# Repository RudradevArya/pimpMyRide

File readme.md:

# Pimp My Ride - Part 3

## Arduino Speedometer and NeoPixel FastLED Strip

This project combines a speedometer functionality with an LED light controller for a bicycle or similar vehicle. It uses an Arduino board to read speed data from a magnetic sensor and control a series of LED light patterns.

## Project Progress Videos

## Task List

Here's a task list for further development of the project:

* [x] iNtErgRaTiOn (just for making fun of myself bcz in a hurry i couldn't type "integration" properly)
* [x] Implement basic speedometer functionality
* [x] Set up LCD display for speed and distance
* [x] Integrate WS2812B LED strip control
* [x] Create multiple LED patterns
* [x] Implement brake light feature
* [ ] Optimize code for better performance
* [ ] Implement power-saving features
* [x] Create a PCB design for a more compact build
* [ ] Develop a weatherproof enclosure
* [ ] Add Bluetooth connectivity for mobile app control
* [ ] Implement data logging feature
* [ ] Create user manual and assembly instructions
* [x] ✨**ENJOY**✨

## Features

1. Speedometer
    * Calculates and displays current speed
    * Tracks total distance traveled
    * Shows total time in motion
2. LED Light Controller
    * Multiple light patterns for visibility and aesthetics
    * Turn signal and brake light functionality
    * Customizable LED colors and patterns

## Hardware Requirements

* Arduino board (e.g., Arduino Uno)
* LCD display (16x2 characters)
* Magnetic sensor (Hall effect sensor)
* WS2812B LED strip
* Buttons for mode selection and turn signals
* Appropriate resistors and wiring

For a complete list of parts, refer to `tinkerCADParts list.png` in the project root.

## Wiring Diagram and Schematic

* The circuit diagram can be found in `tinkerCAD circuit diagram.png`
* The schematic is available in `tinker_cad-schematics.png`
* For the PCB design, refer to `KiCAD PCB screenshot.png`

For the most up-to-date schematic and PCB design, open the following files in KiCad:

* Schematic: `intergration/integration-arduino-shield/integration.kicad_sch`
* PCB: `intergration/integration-arduino-shield/integration.kicad_pcb`

## Libraries Used

* FastLED
* LiquidCrystal

## Pin Configuration

* LCD: pins 13, 12, 11, 10, 9, 8
* Magnetic sensor: pin 7
* LED strip data: pin 3
* Right turn signal button: pin 4
* Left turn signal button: pin 5
* Brake signal: pin 2
* Mode selection button: pin 13
* Main control button: pin 12

## Setup

1. Connect all components according to the pin configuration.
2. Install the required libraries in your Arduino IDE.
3. Upload the provided code to your Arduino board.
4. Adjust the `Wheel_circumference_in_Cm` constant to match your wheel size.

## Usage

* The speedometer will automatically start tracking when motion is detected.
* Use the mode selection button to cycle through different LED patterns.
* Use the turn signal buttons to activate left or right turn signals.
* The brake light will activate automatically when the brake signal is received.

## Customization

You can customize the LED patterns by modifying the `Pattern1()` through `Pattern9()` functions in the code. Adjust colors, timing, and sequences to create your desired effects.

## Project Structure

``` bash
PimpMyRide/
│
├── intergration/
│   ├── integration-arduino-shield/ (run the .pcb & .sch files from here)
│       ├── integration.kicad_sch
│       ├── integration.kicad_pcb
│
├── intergration.ino (the main arduino file to run)
├── tinkerCAD circuit diagram.png
├── tinkerCADParts list.png
├── tinker_cad-schematics.png
├── KiCAD PCB screenshot.png
└── README.md
```

## Note

This project combines multiple functionalities and may require fine-tuning based on your specific hardware setup and requirements. Always ensure proper visibility and adhere to local regulations when using this on public roads.

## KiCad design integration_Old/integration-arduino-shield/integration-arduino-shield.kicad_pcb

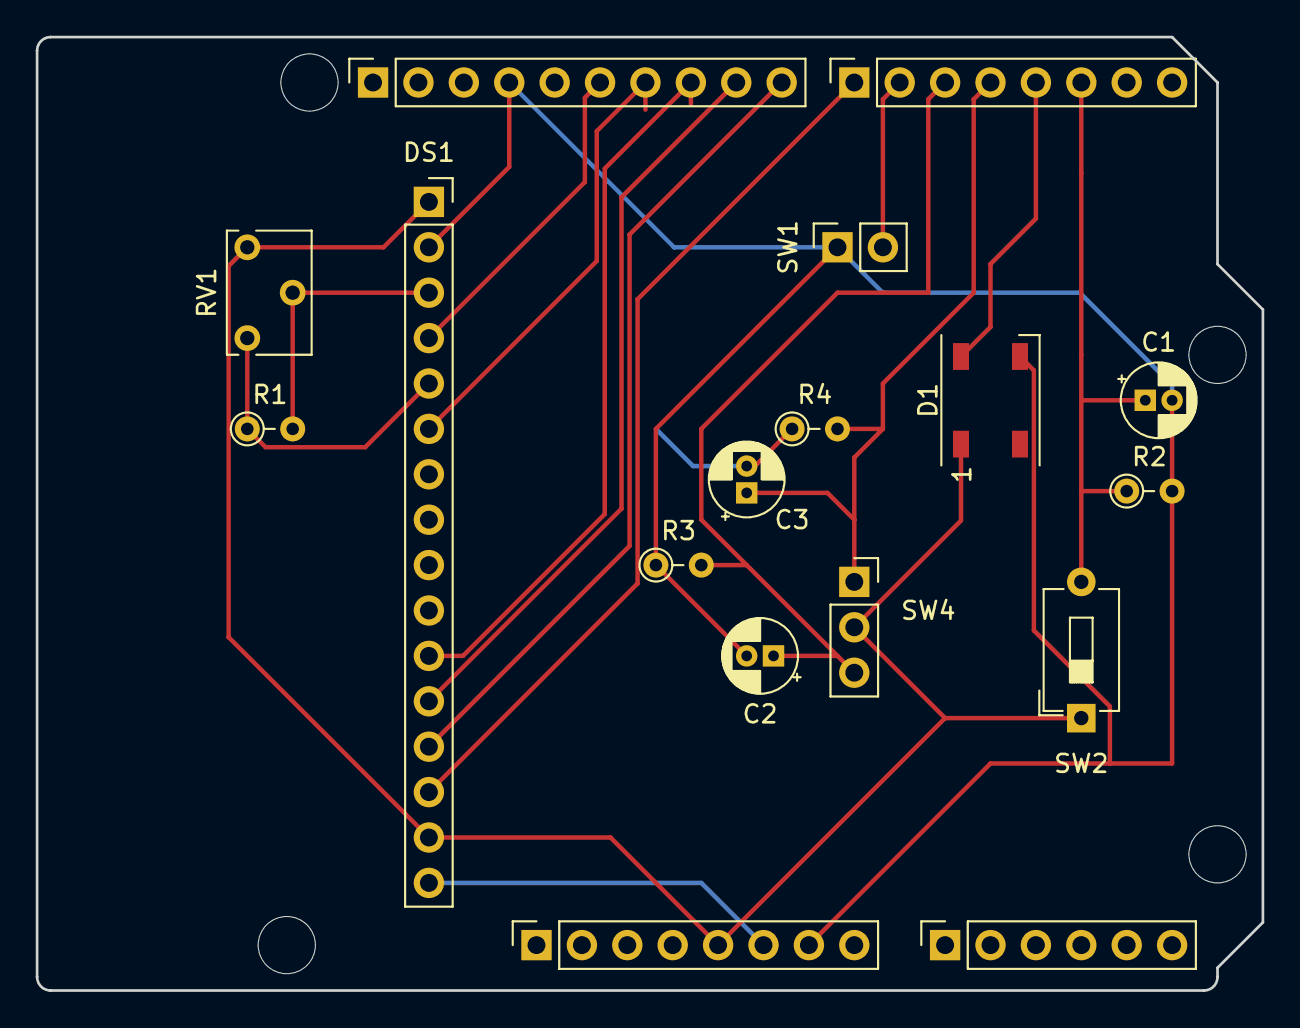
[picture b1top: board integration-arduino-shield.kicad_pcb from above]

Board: 2 copper layers, 68.6 x 53.3 mm, 21 parts (0 on the bottom side), 14 nets.

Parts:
C1, C2, C3: C_Polarized; CP_Radial_D4.0mm_P1.50mm
D1: WS2812B; LED_WS2812B_PLCC4_5.0x5.0mm_P3.2mm
DS1: WC1602A; PinSocket_1x16_P2.54mm_Vertical
J1: Power; PinSocket_1x08_P2.54mm_Vertical
J2: Digital/PWM; PinSocket_1x10_P2.54mm_Vertical
J3: Analog; PinSocket_1x06_P2.54mm_Vertical
J4: Digital/PWM; PinSocket_1x08_P2.54mm_Vertical
MH1, MH2, MH3, MH4: MountingHole_3.2mm
R1, R2, R3, R4: R; R_Axial_DIN0204_L3.6mm_D1.6mm_P2.54mm_Vertical
RV1: R_Potentiometer; Potentiometer_Bourns_3266W_Vertical
SW1: SW_Reed; PinSocket_1x02_P2.54mm_Vertical
SW2: SW_Push; SW_DIP_SPSTx01_Slide_6.7x4.1mm_W7.62mm_P2.54mm_LowProfile
SW4: SW_SPDT_MSM; PinSocket_1x03_P2.54mm_Vertical

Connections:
+5V: D1.1 (VDD), DS1.1 (VSS), DS1.15 (LED(+)), J1.5, RV1.1, SW2.1, SW4.2
/2: C1.1, J4.6, R2.1, SW2.2
/4: C3.1, J4.4, R4.2, SW4.1
/7: DS1.14 (D7), J4.1
/8: DS1.13 (D6), J2.10
/12: DS1.4 (RS), J2.6
/*3: D1.4 (DIN), J4.5
/*5: C2.1, J4.3, R3.2, SW4.3
/*6: J4.2, SW1.2
/*9: DS1.12 (D5), J2.9
/*10: DS1.11 (D4), J2.8
/*11: DS1.6 (E), J2.7
GND: C1.2, C2.2, C3.2, D1.3 (VSS), DS1.2 (VDD), DS1.5 (R/W), DS1.16 (LED(-)), J1.6, J1.7, J2.4, R1.1, R2.2, R3.1, R4.1, RV1.3, SW1.1
unnamed: DS1.3 (VO), R1.2, RV1.2

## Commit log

2023-08-15 new folder lets see if this works
2023-08-15 added tinker cad circuit diagram, parts and schema
2023-08-15 added pcb design and schematics for the arduino shield
2023-08-15 trying to add all kiCAD foldersand files
2024-07-24 added PCB screenshot and extra files
2024-07-24 added readme, cleaner folder structure, working pcb files
